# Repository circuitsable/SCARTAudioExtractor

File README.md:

# SCARTAudioExtractor
This is a PCB that acts as a SCART female-to-female coupler/gender changer, but extracts the audio from the input to a 3.5mm TRS jack, with multiple SCART variations available.
- Euro to Euro Extract (you probably want this one)
- JP21 to Euro Extract

# Why/About

I have several older game consoles that output their video and audio over SCART, and I often want to listen to the game audio with headphones.

I designed this board because the few products that extract audio from a SCART cable either terminate to RCA jacks, are out of stock, or do not support RGB.

This board must be right before your display! Audio is completely removed from the SCART cable, and you will not get audio from the output SCART connector. This coupler also does not support daisy chaining and removes the mostly unused D2B bus signals as well.

Create an issue if you would like a version that uses RCA jacks or JP-21.

# What you'll need

The PCB, of which gerbers are available for in the [releases](https://github.com/circuitsable/SCARTAudioExtractor/releases/tag/gerbers). The PCB can be ordered from any board house, some examples of which are [Oshpark](https://oshpark.com/#services), [PCBWay](https://www.pcbway.com/QuickOrderOnline.aspx) or [JLCPCB](https://cart.jlcpcb.com/quote).

2 Female SCART Connectors (specifically, [KYCON_SCART_K-SCARTX-022_Horizontal](https://www.mouser.com/datasheet/2/222/K-SCARTX-022-183347.pdf)). No major suppliers carry SCART connectors anymore as far as I'm aware, you can find listings on Aliexpress [here (LR Ear)](https://www.aliexpress.us/item/3256803860252051.html), [here (VER3)](https://www.aliexpress.us/item/2255800585241541.html) or [here (03)](https://www.aliexpress.us/item/3256806450160956.html). Ensure that the part that juts out is on the top (opposite side of the pins), the connector has ears, is a horizontal/90 degree connector, has all 21 pins (to ensure RGB support), and does not have any extra mounting methods besides the ears (e.g, screw holes).

1 Female 3.5mm TRS Jack (specifically, [Jack_3.5mm_CUI_SJ1-3523N_Horizontal](https://www.cuidevices.com/product/resource/pdf/sj1-352xn.pdf)). This can be bought from [Mouser](https://www.mouser.com/ProductDetail/CUI-Devices/SJ1-3523N?qs=WyjlAZoYn50aNl0vAhb3Tg%3D%3D), [Digikey](https://www.digikey.com/en/products/detail/cui-devices/SJ1-3523N/738689) or Aliexpress [here](https://www.aliexpress.us/item/2251832685563184.html), [here](https://www.aliexpress.us/item/3256803939752840.html) or [here](https://www.aliexpress.us/item/3256805272161608.html).

Basic soldering equipment.

(Optional) Rubber feet or a case of some sort

# PCB Images

# TODO

Design a 3D printable shell to protect against shorts/damage to the board.

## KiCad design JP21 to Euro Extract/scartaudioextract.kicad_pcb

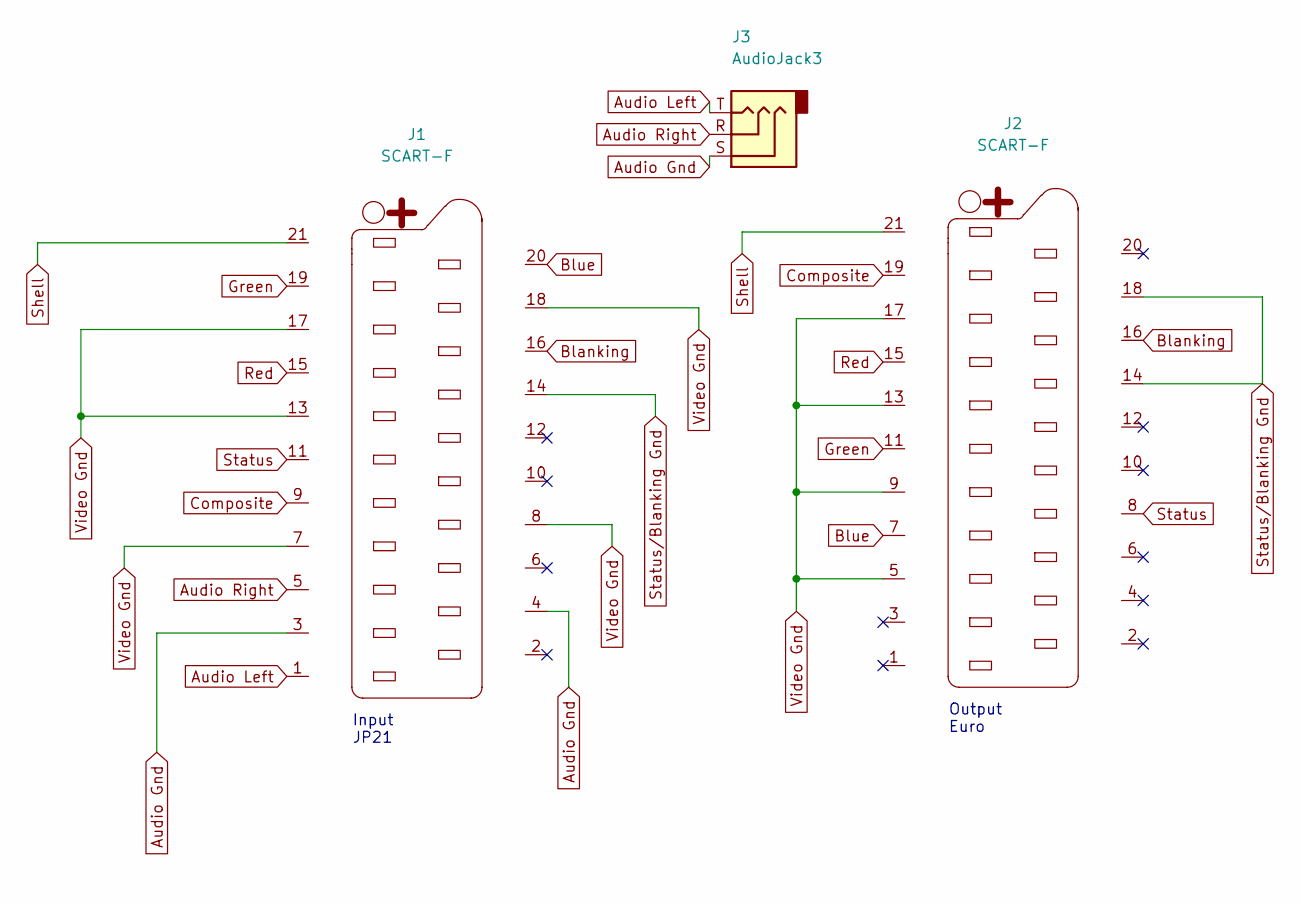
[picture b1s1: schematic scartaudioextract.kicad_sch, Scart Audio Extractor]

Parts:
J1, J2: SCART-F; KYCON_SCART_K-SCARTX-022_Horizontal
J3: AudioJack3; Jack_3.5mm_CUI_SJ1-3523N_Horizontal

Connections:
Audio Gnd: J1.3, J1.4, J3.S
Audio Left: J1.1, J3.T
Audio Right: J1.5, J3.R
Blanking: J1.16, J2.16
Blue: J1.20, J2.7
Composite: J1.9, J2.19
Green: J1.19, J2.11
Red: J1.15, J2.15
Shell: J1.21, J2.21
Status: J1.11, J2.8
Status/Blanking Gnd: J1.14, J2.14, J2.18
Video Gnd: J1.7, J1.8, J1.13, J1.17, J1.18, J2.5, J2.9, J2.13, J2.17

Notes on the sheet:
Input JP21
Output Euro

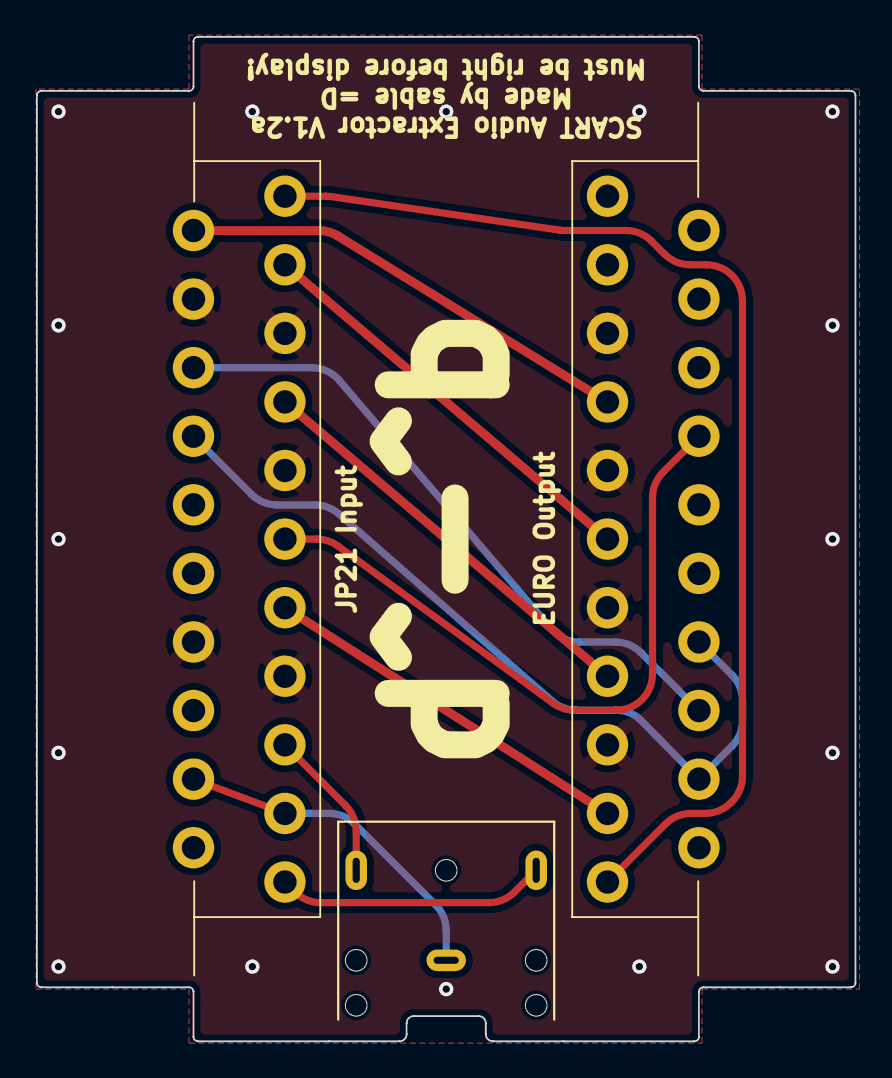
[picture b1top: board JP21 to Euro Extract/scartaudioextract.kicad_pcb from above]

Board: 2 copper layers, 45.5 x 55.8 mm, 3 parts (0 on the bottom side), 12 nets.

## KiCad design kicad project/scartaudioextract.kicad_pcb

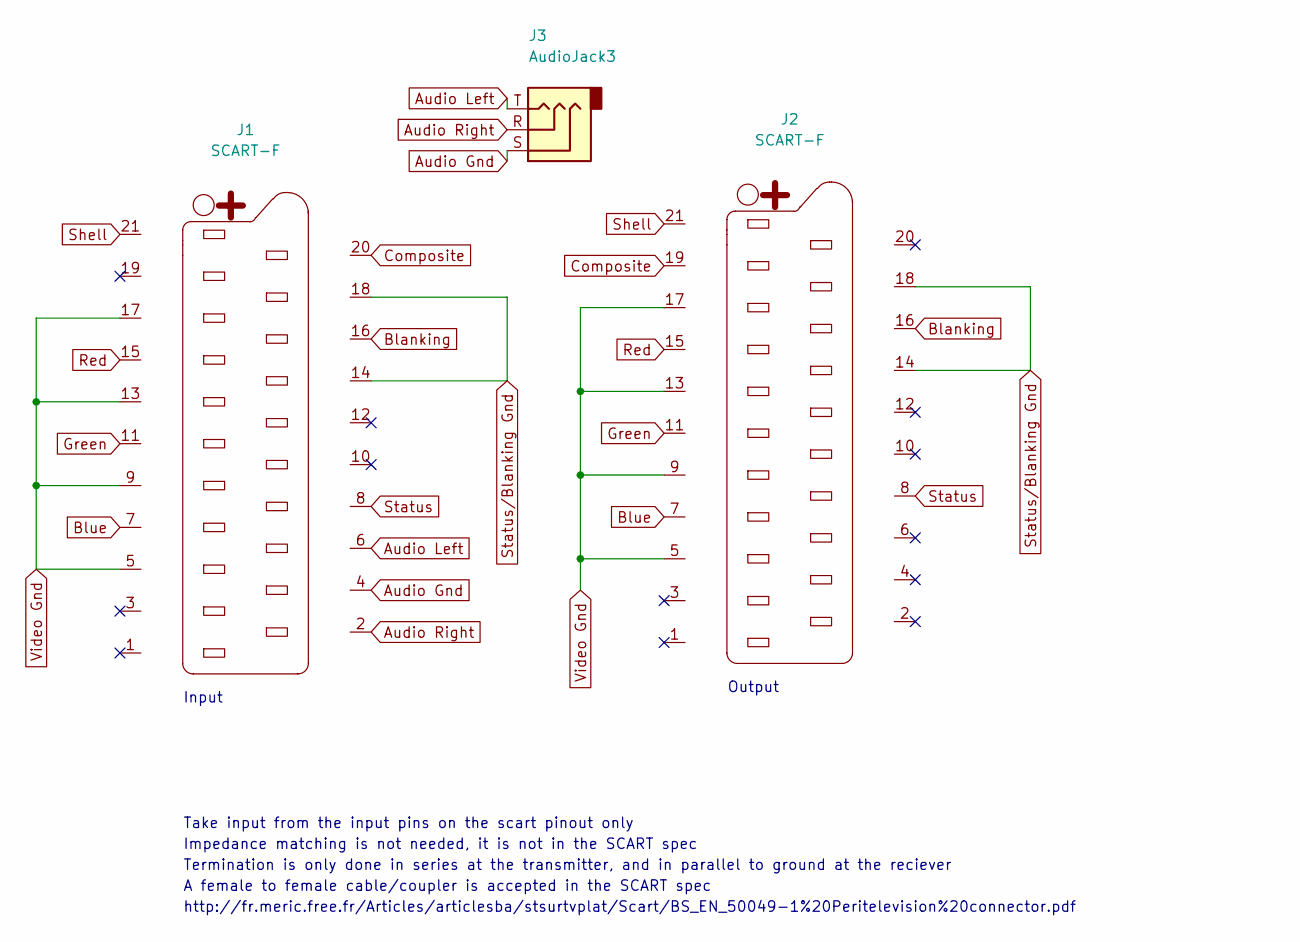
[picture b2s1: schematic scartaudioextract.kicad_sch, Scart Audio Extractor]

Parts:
J1, J2: SCART-F; KYCON_SCART_K-SCARTX-022_Horizontal
J3: AudioJack3; Jack_3.5mm_CUI_SJ1-3523N_Horizontal

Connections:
Audio Gnd: J1.4, J3.S
Audio Left: J1.6, J3.T
Audio Right: J1.2, J3.R
Blanking: J1.16, J2.16
Blue: J1.7, J2.7
Composite: J1.20, J2.19
Green: J1.11, J2.11
Red: J1.15, J2.15
Shell: J1.21, J2.21
Status: J1.8, J2.8
Status/Blanking Gnd: J1.14, J1.18, J2.14, J2.18
Video Gnd: J1.5, J1.9, J1.13, J1.17, J2.5, J2.9, J2.13, J2.17

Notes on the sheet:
Take input from the input pins on the scart pinout only
Termination is only done in series at the transmitter, and in parallel to ground at the reciever
Input
Output
http://fr.meric.free.fr/Articles/articlesba/stsurtvplat/Scart/BS_EN_50049-1%20Peritelevision%20connector.pdf
Impedance matching is not needed, it is not in the SCART spec
A female to female cable/coupler is accepted in the SCART spec

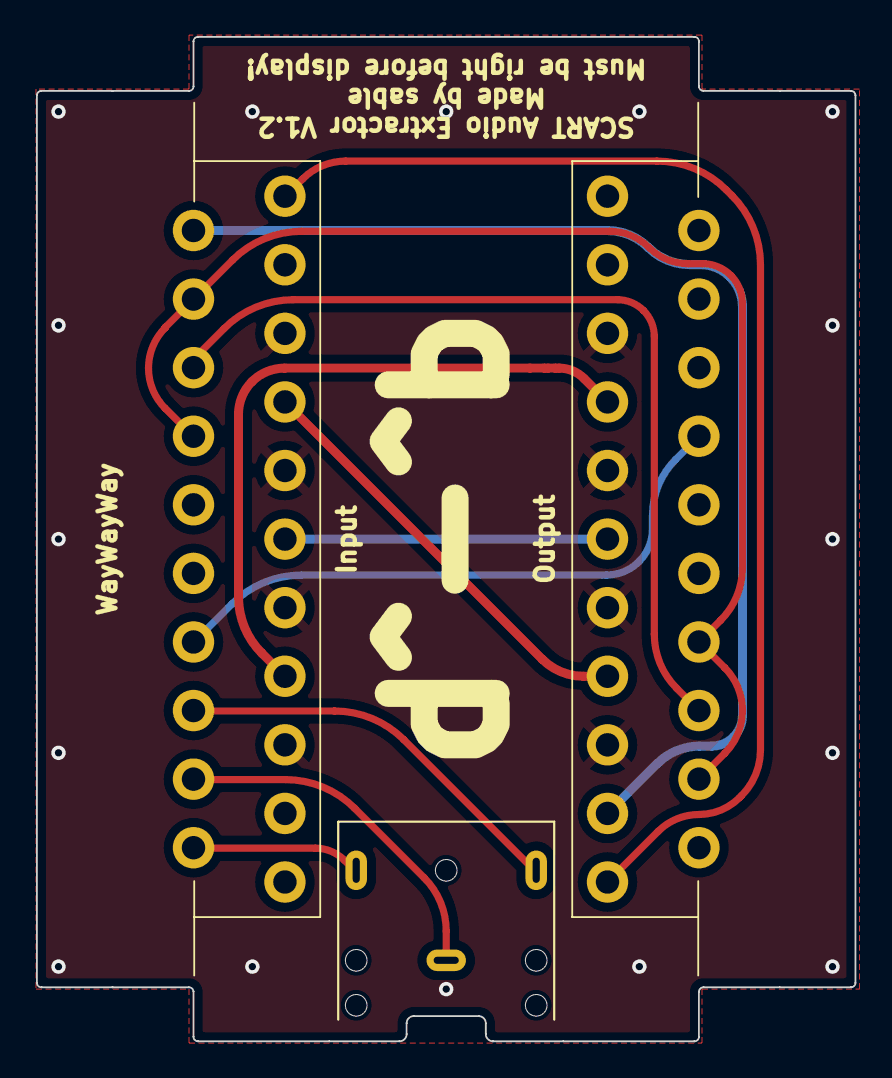
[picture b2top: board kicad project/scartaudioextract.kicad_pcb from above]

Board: 2 copper layers, 45.5 x 55.8 mm, 3 parts (0 on the bottom side), 12 nets.

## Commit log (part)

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2024-08-22 photos
2024-08-22 Add gerbers
2024-08-22 Add KiCad Project
2024-08-22 Create LICENSE
2024-08-24 add termination resistors
2024-08-24 add schematic
2024-08-24 add datasheets
2024-08-25 remove termination resistors
2024-08-25 forgot a connection
2024-08-25 add extra info
2024-08-30 improve schematic, use better design rules
2024-08-30 new gerbers
2024-09-11 clarify euroscart
2024-10-10 add assembled board image
2024-11-30 probably works!
2024-12-29 works :D
